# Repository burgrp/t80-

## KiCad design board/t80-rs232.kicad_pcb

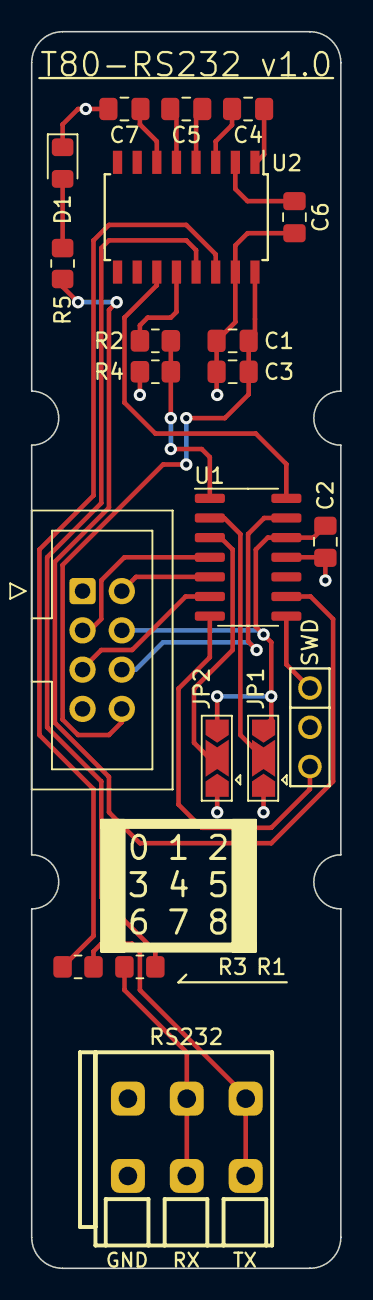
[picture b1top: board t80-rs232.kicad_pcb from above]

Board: 2 copper layers, 20.0 x 80.0 mm, 20 parts (0 on the bottom side), 26 nets.

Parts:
C1, C4, C5, C6, C7: 1u; C_0805_2012Metric_Pad1.18x1.45mm_HandSolder
C2, C3: 100n; C_0805_2012Metric_Pad1.18x1.45mm_HandSolder
D1: LED; LED_0805_2012Metric_Pad1.15x1.40mm_HandSolder
J2: RS232; DG235-3.81-03P
JP1, JP2: A1; SolderJumper-3_P2.0mm_Open_TrianglePad1.0x1.5mm
R1, R2, R3, R4, R5: 270R; R_0805_2012Metric_Pad1.20x1.40mm_HandSolder
U1: ATSAMD09C13A-SS; SOIC-14_3.9x8.7mm_P1.27mm
U2: MAX232; SOIC-16W_5.3x10.2mm_P1.27mm
X1: SWD
X2: IDC-Header_2x04_P2.54mm_Vertical

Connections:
+3V3: C2.2, JP1.3 (B), JP2.3 (B), U1.12 (VDD), X2.4 (3V3)
+5V: C1.2, C3.2, U2.16 (VCC), X2.8 (5V)
/A1: JP1.2 (C), U1.2 (PA08/XIN)
/A2: JP2.2 (C), U1.3 (PA09/XOUT)
/IRQ: U1.13 (PA02), X2.6 (IRQ)
/LED: R5.1, U1.9 (PA24)
/RST: U1.6 (PA28/~RST), X2.5 (RST)
/RX_3V: R2.1, R4.2, U1.1 (PA05)
/RX_RS232: J2.2, R3.2
/SCL: U1.5 (PA15), X2.2 (SCL)
/SDA: U1.4 (PA14), X2.3 (SDA)
/SWCLK: U1.7 (PA30/SWCLK), X1.3 (SWCLK)
/SWDIO: U1.8 (PA31/SWDIO), X1.1 (SWDIO)
/TX_3V: U1.14 (PA04), U2.11 (T1IN)
/TX_RS232: J2.3, R1.2
GND: C1.1, C2.1, C3.1, C6.2, C7.2, D1.1 (K), J2.1, JP1.1 (A), JP2.1 (A), R4.1, U1.11 (GND), U2.15 (GND), X1.2 (GND), X2.1 (GND), X2.7 (GND)
unnamed: D1.2 (A), R5.2
unnamed: C4.1, U2.1 (C1+)
unnamed: C4.2, U2.3 (C1-)
unnamed: C5.1, U2.4 (C2+)
unnamed: C5.2, U2.5 (C2-)
unnamed: R3.1, U2.13 (R1IN)
unnamed: R2.2, U2.12 (R1OUT)
unnamed: R1.1, U2.14 (T1OUT)
unnamed: C6.1, U2.2 (VS+)
unnamed: C7.1, U2.6 (VS-)
